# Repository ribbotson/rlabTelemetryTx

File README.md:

rlabTelemetryTx
===============

rlab Telemetry Transmitter

This repository contains code, hardware information and data relating to the rlab Telemetry Transmittter.

The rlab Telemetry Transmitter is an ATXMega128A4U based development board for High altitude Balloon tracking and telemetry.
The transmitter is a Radiometrix NTX2B 434MHz module and the GPS is the Ublox7q. The board is programmed using Atmel DFU over the
USB .

Software is based around the Atmel Software Framework ASF.

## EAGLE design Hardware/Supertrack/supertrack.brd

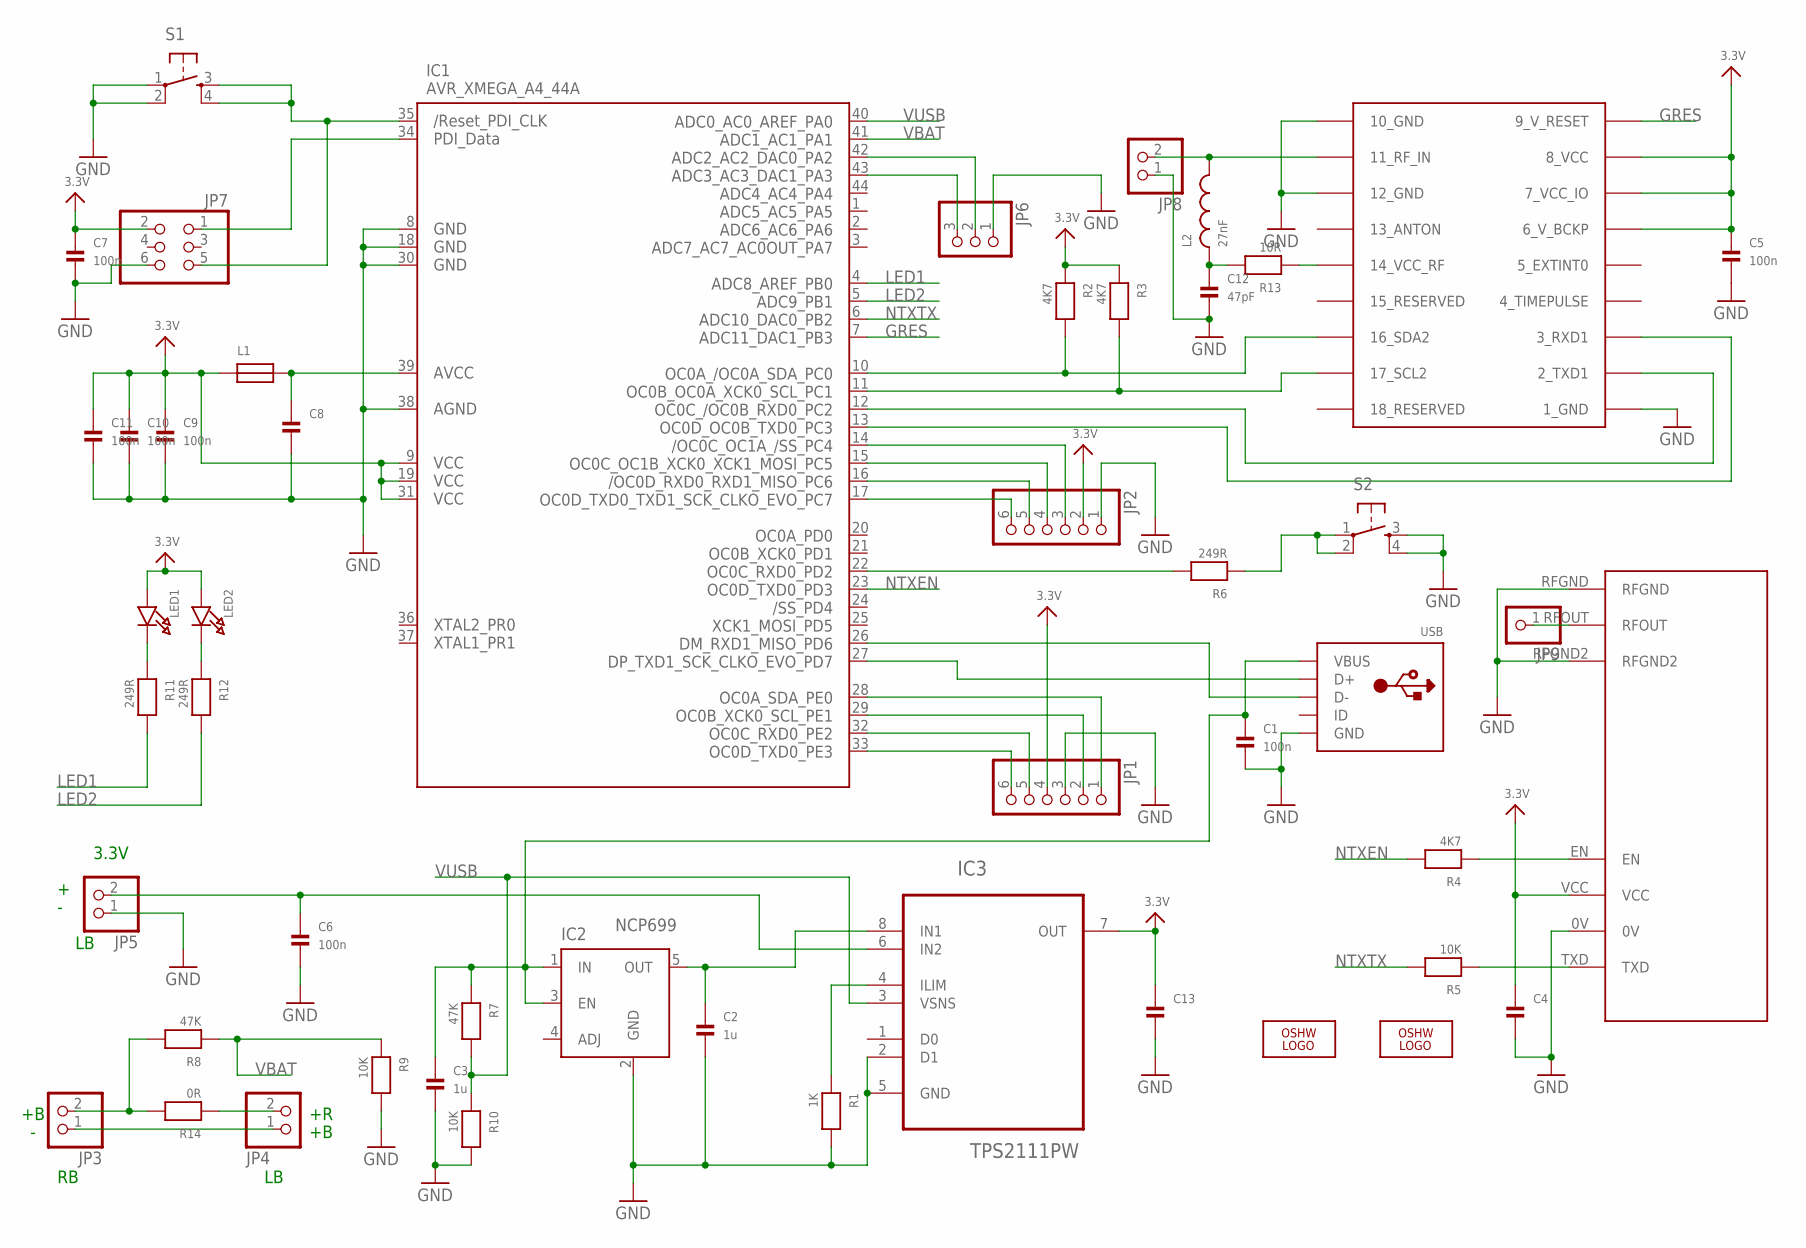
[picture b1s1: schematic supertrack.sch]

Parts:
C1, C5, C6, C7, C9, C10, C11: 100n; 0603
C2, C3: 1u; 0603
C4, C8, C13: CAP_CERAMIC0603; 0603
C12: 47pF; 0603
IC1: AVR_XMEGA_A4_44A; TQFP44
IC2: NCP699; SOT23-5
IC3: TPS2111PW; SOP65P640X120-8N
JP1, JP2: PINHD-1X6; 1X06
JP3, JP4, JP5: PINHD-1X2; 1X02
JP6: PINHD-1X3; 1X03
JP7: PINHD-2X3; 2X03
JP8: HEADER-1X2ROUND; 1X02_ROUND
JP9: HEADER-1X1ROUND; 1X01_ROUND
L1: FERRITE; 0603
L2: 27nF; 0603
LED1, LED2: LED0603; CHIPLED_0603
LOGO1: OSHW_LOGO_8MILX0150-NT; OSHW_8X150_NOTEXT
LOGO2: OSHW_LOGO_8MILX0100-NT; OSHW_8X100_NOTEXT
R1: 1K; 0603
R2, R3, R4: 4K7; 0603
R5, R9, R10: 10K; 0603
R6, R11, R12: 249R; 0603
R7, R8: 47K; 0603
R13: 10R; 0603
R14: 0R; 0603
S1, S2: TAC_SWITCHSMD; TACTILE_SWITCH_SMD
U$1: NTX2
U$2: UBLOX_MAX
USB: USBMINIB; USB-MINIB

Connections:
3.3V: C4.1, C5.1, C7.1, C9.1, C10.1, C11.1, C13.1, IC1.9 (VCC1), IC1.19 (VCC2), IC1.31 (VCC3), IC3.7 (OUT), JP1.4, JP2.2, JP7.2, L1.1, LED1.A, LED2.A, R2.1, R3.1, U$1.VCC, U$2.6_V_BCKP, U$2.7_VCC_IO, U$2.8_VCC
GND: C1.2, C2.2, C3.2, C4.2, C5.2, C6.2, C7.2, C8.2, C9.2, C10.2, C11.2, C12.2, C13.2, IC1.8 (GND1), IC1.18 (GND2), IC1.30 (GND3), IC1.38 (AGND), IC2.2 (GND), IC3.2 (D1), IC3.5 (GND), JP1.3, JP2.1, JP5.1, JP6.1, JP7.6, JP8.1, R1.2, R9.2, R10.2, S1.1, S1.2, S2.3, S2.4, U$1.0V, U$1.RFGND, U$1.RFGND2, U$2.1_GND, U$2.10_GND, U$2.12_GND, USB.GND
GRES: IC1.7 (PB3), U$2.9_V_RESET
LED1: IC1.4 (PB0), R11.2
LED2: IC1.5 (PB1), R12.2
unnamed: C2.1, IC2.5 (OUT), IC3.8 (IN1)
unnamed: IC1.33 (PE3), JP1.6
unnamed: IC1.32 (PE2), JP1.5
unnamed: C6.1, IC3.6 (IN2), JP5.2
unnamed: R6.1, S2.1, S2.2
unnamed: IC1.26 (PD6), USB.D-
unnamed: IC1.27 (PD7), USB.D+
unnamed: IC1.22 (PD2), R6.2
unnamed: R5.1, U$1.TXD
unnamed: R4.1, U$1.EN
unnamed: JP9.1, U$1.RFOUT
unnamed: C1.1, C3.1, IC2.1 (IN), IC2.3 (EN), R7.1, USB.VBUS
unnamed: IC3.4 (ILIM), R1.1
unnamed: IC1.10 (PC0), R2.2, U$2.16_SDA2
unnamed: IC1.11 (PC1), R3.2, U$2.17_SCL2
unnamed: IC1.12 (PC2), U$2.2_TXD1
unnamed: IC1.13 (PC3), U$2.3_RXD1
unnamed: LED2.C, R12.1
unnamed: LED1.C, R11.1
unnamed: IC1.29 (PE1), JP1.2
unnamed: IC1.28 (PE0), JP1.1
unnamed: IC1.17 (PC7), JP2.6
unnamed: IC1.16 (PC6), JP2.5
unnamed: IC1.15 (PC5), JP2.4
unnamed: IC1.14 (PC4), JP2.3
unnamed: JP3.1, JP4.1
unnamed: JP4.2, R14.1
unnamed: IC1.34 (PDI_DATA), JP7.1
unnamed: IC1.35 (RESET), JP7.5, S1.3, S1.4
unnamed: IC1.42 (PA2), JP6.2
unnamed: IC1.43 (PA3), JP6.3
unnamed: JP8.2, L2.2, U$2.11_RF_IN
unnamed: C12.1, L2.1, R13.2
unnamed: R13.1, U$2.14_VCC_RF
unnamed: C8.1, IC1.39 (AVCC), L1.2
NTXEN: IC1.23 (PD3), R4.2
NTXTX: IC1.6 (PB2), R5.2
VBAT: IC1.41 (PA1), R8.1, R9.1
VIN: JP3.2, R8.2, R14.2
VUSB: IC1.40 (PA0), IC3.3 (VSNS), R7.2, R10.1

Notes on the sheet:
3.3V

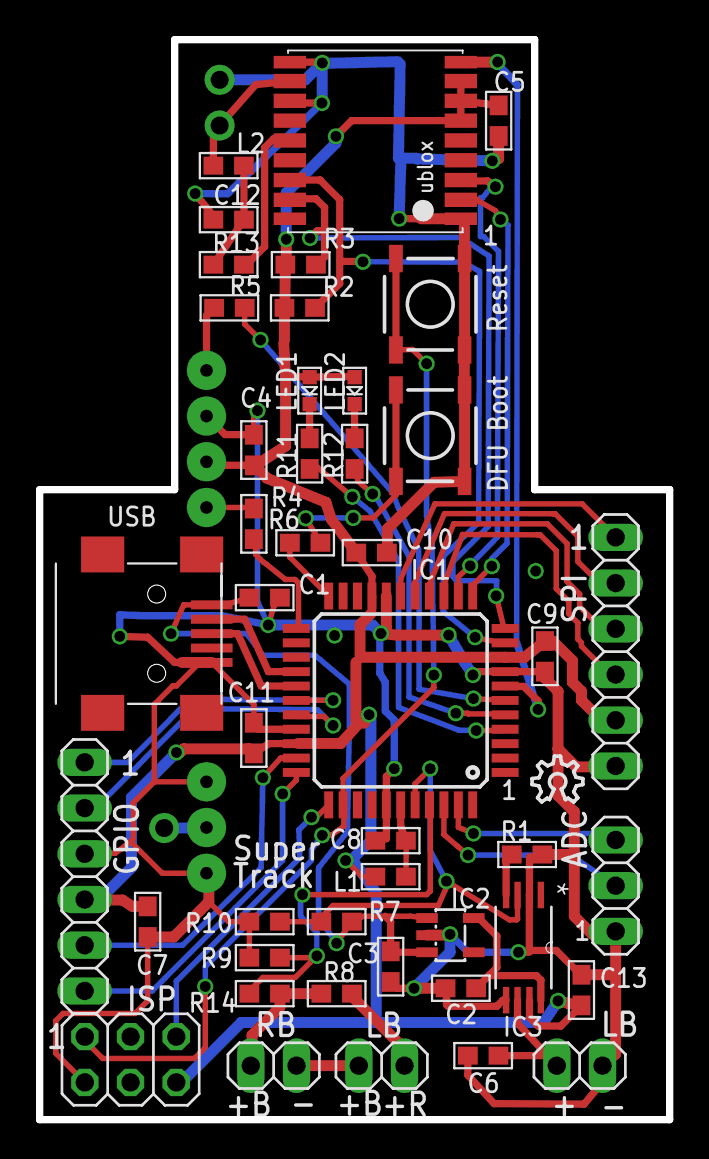
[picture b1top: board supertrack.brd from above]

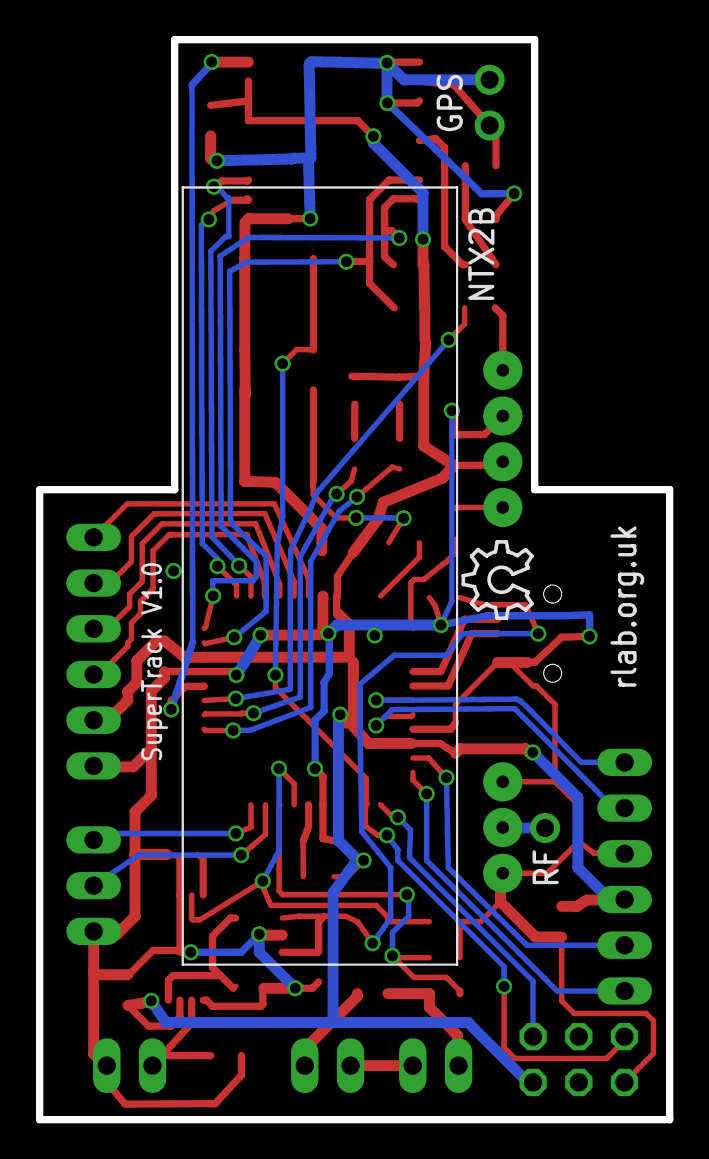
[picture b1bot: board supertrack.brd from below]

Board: 2 copper layers, 35.0 x 60.0 mm, 50 parts (2 on the bottom side), 45 nets.

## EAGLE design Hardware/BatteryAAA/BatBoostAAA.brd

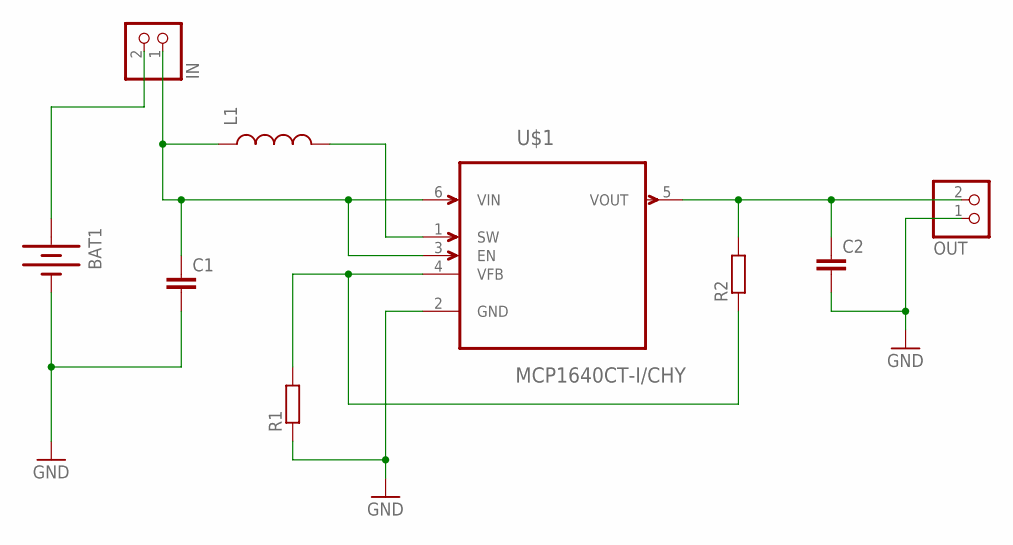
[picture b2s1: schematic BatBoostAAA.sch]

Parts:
BAT1: BATTERYAAA; BATTERY-AAA
C1, C2: C-EUC0805K; C0805K
IN: PINHD-1X2; 1X02
L1: INDUCTOR1210; LQH32
OUT: PINHD-1X2; 1X02
R1, R2: R-EU_R0603; R0603
U$1: MCP1640CT-I/CHY; SOT95P270X145-6N

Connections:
GND: BAT1.GND@1 (-), C1.2, C2.2, OUT.1, R1.1, U$1.2 (GND)
unnamed: C1.1, IN.1, L1.1, U$1.3 (EN), U$1.6 (VIN)
unnamed: C2.1, OUT.2, R2.2, U$1.5 (VOUT)
unnamed: R1.2, R2.1, U$1.4 (VFB)
unnamed: L1.2, U$1.1 (SW)
unnamed: BAT1.PWR@1 (+), IN.2

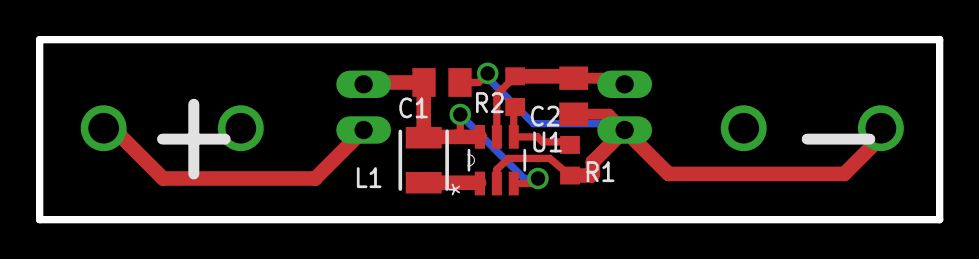
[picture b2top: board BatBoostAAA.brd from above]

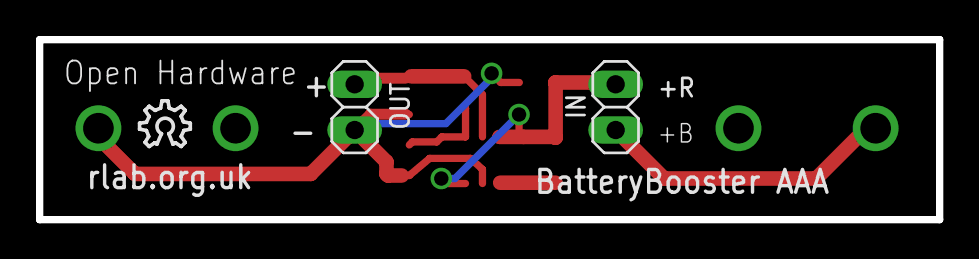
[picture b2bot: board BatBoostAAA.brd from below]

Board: 2 copper layers, 50.0 x 10.0 mm, 10 parts (3 on the bottom side), 6 nets.

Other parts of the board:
U$2: OSHW_8X100_NOTEXT

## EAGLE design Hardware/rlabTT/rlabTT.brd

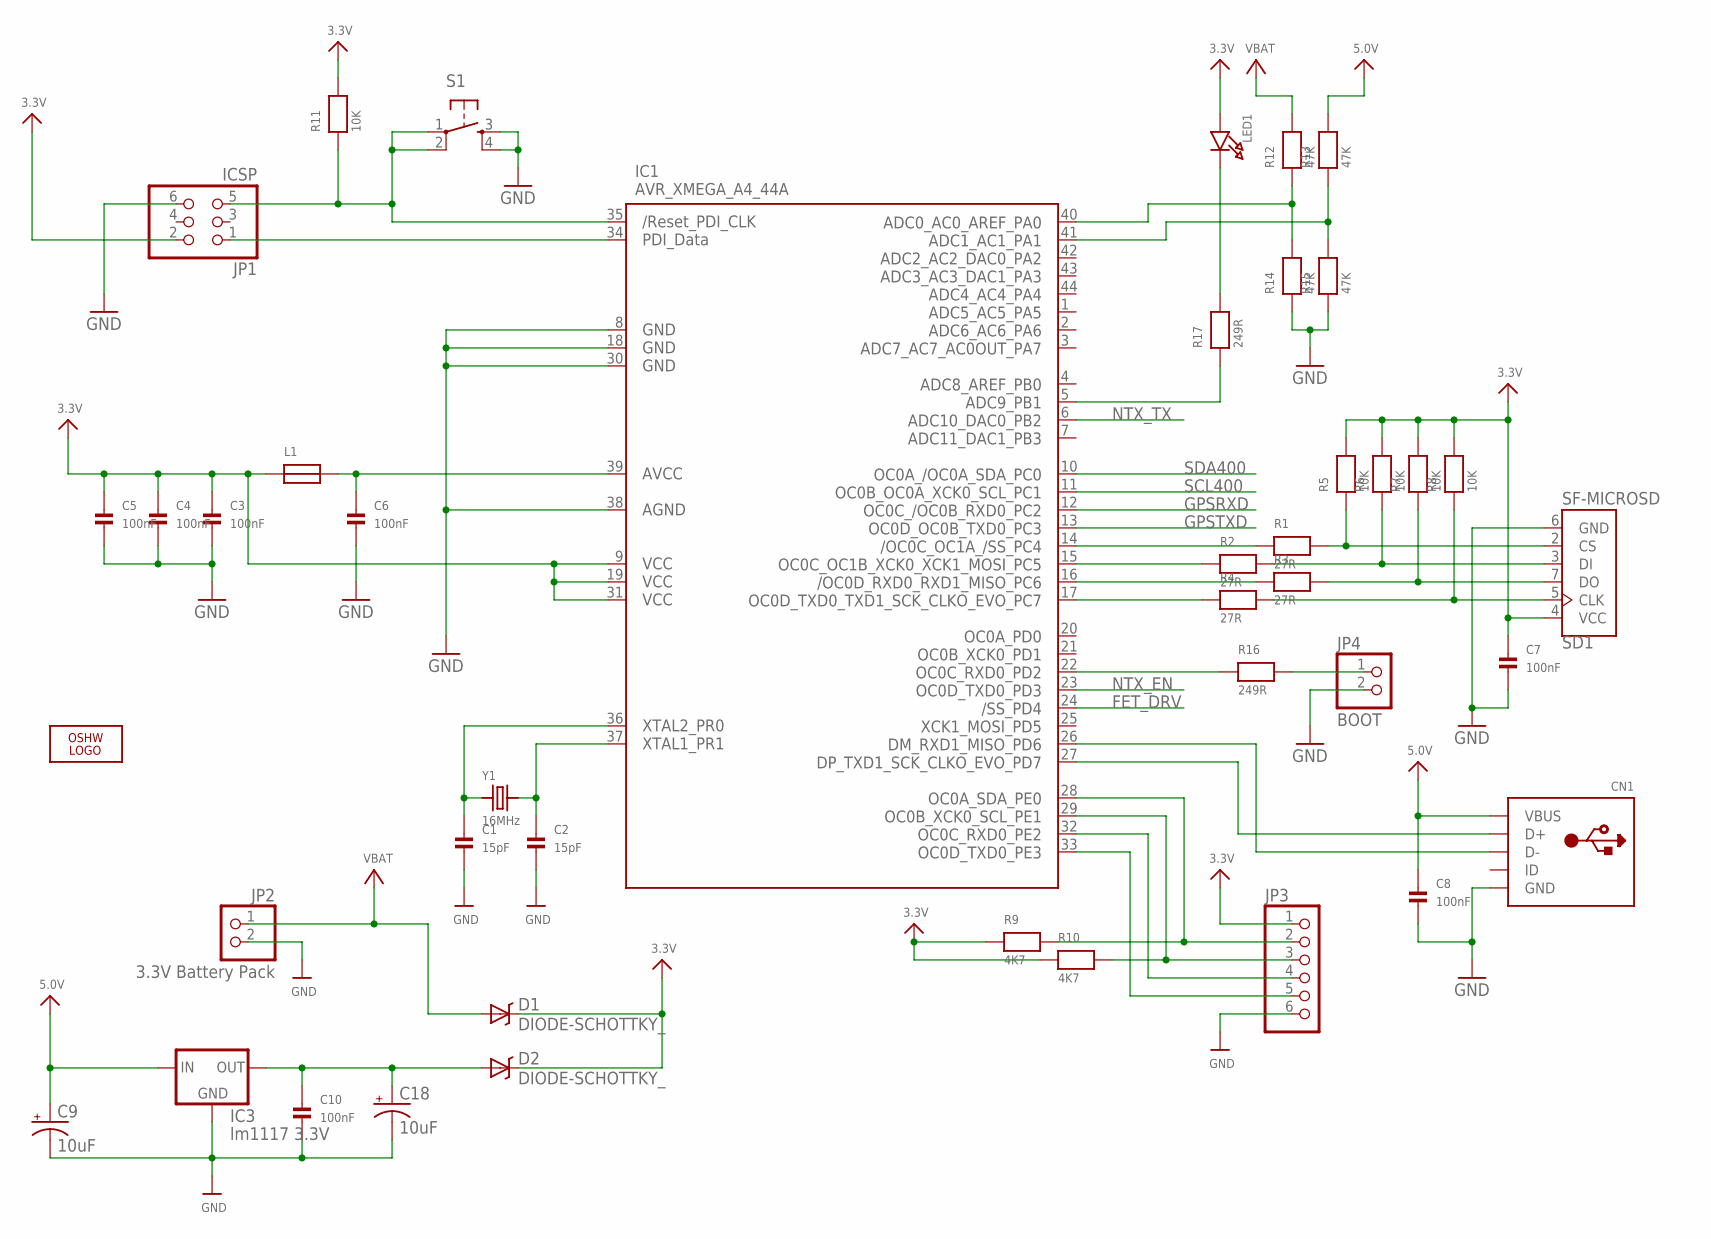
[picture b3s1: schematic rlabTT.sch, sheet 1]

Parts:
C1, C2: 15pF; 0603
C3, C4, C5, C6, C7, C8, C10: 100nF; 0603
C9, C18: 10uF; EIA3528
CN1: USBMINIB; USB-MINIB
D1, D2: DIODE-SCHOTTKY_; SMA-DIODE
IC1: AVR_XMEGA_A4_44A; TQFP44
IC3: lm1117 3.3V; SOT223
JP1: ICSP; 2X03/90
JP2: 3.3V Battery Pack; 1X02/90
JP3: PINHD-1X6/90; 1X06/90
JP4: BOOT; 1X02/90
L1: FERRITE; 0603
LED1: LED0603; CHIPLED_0603
LOGO1: OSHW_LOGO_8MILX0150-NT; OSHW_8X150_NOTEXT
R1, R2, R3, R4: 27R; 0603
R5, R6, R7, R8, R11: 10K; 0603
R9, R10: 4K7; 0603
R12, R13, R14, R15: 47K; 0603
R16, R17: 249R; 0603
S1: TAC_SWITCHSMD; TACTILE_SWITCH_SMD
SD1: SF-MICROSD; MICROSD
Y1: 16MHz; CRYSTAL_3.2X2.5

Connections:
3.3V: C3.1, C4.1, C5.1, C7.1, D1.C, D2.C, IC1.9 (VCC1), IC1.19 (VCC2), IC1.31 (VCC3), JP1.2, JP3.1, L1.1, LED1.A, R5.2, R6.2, R7.2, R8.2, R9.1, R10.1, R11.2, SD1.4 (VCC); also elsewhere on the board
5.0V: C8.1, C9.A (+), CN1.VBUS, IC3.3 (IN), R13.2
FET_DRV: IC1.24 (PD4); also elsewhere on the board
GND: C1.2, C2.2, C3.2, C4.2, C5.2, C6.2, C7.2, C8.2, C9.C (-), C10.2, C18.C (-), CN1.GND, IC1.8 (GND1), IC1.18 (GND2), IC1.30 (GND3), IC1.38 (AGND), IC3.1 (GND), JP1.6, JP2.2, JP3.6, JP4.2, R14.1, R15.1, S1.3, S1.4, SD1.6 (GND); also elsewhere on the board
GPSRXD: IC1.12 (PC2); also elsewhere on the board
GPSTXD: IC1.13 (PC3); also elsewhere on the board
unnamed: IC1.40 (PA0), R12.1, R14.2
unnamed: IC1.22 (PD2), R16.1
unnamed: IC1.41 (PA1), R13.1, R15.2
unnamed: JP4.1, R16.2
unnamed: IC1.5 (PB1), R17.1
unnamed: LED1.C, R17.2
unnamed: C2.1, IC1.37 (PR1), Y1.2
unnamed: C1.1, IC1.36 (PR0), Y1.1
unnamed: C6.1, IC1.39 (AVCC), L1.2
unnamed: IC1.14 (PC4), R1.1
unnamed: CN1.D+, IC1.27 (PD7)
unnamed: CN1.D-, IC1.26 (PD6)
unnamed: IC1.15 (PC5), R2.1
unnamed: IC1.16 (PC6), R3.1
unnamed: IC1.17 (PC7), R4.1
unnamed: R1.2, R5.1, SD1.2 (CS)
unnamed: R2.2, R6.1, SD1.3 (DI)
unnamed: R3.2, R7.1, SD1.7 (DO)
unnamed: IC1.35 (RESET), JP1.5, R11.1, S1.1, S1.2
unnamed: IC1.34 (PDI_DATA), JP1.1
unnamed: C10.1, C18.A (+), D2.A, IC3.2 (OUT)
unnamed: IC1.28 (PE0), JP3.2, R9.2
unnamed: IC1.29 (PE1), JP3.3, R10.2
unnamed: IC1.32 (PE2), JP3.4
unnamed: IC1.33 (PE3), JP3.5
NTX_EN: IC1.23 (PD3); also elsewhere on the board
NTX_TX: IC1.6 (PB2); also elsewhere on the board
SCL400: IC1.11 (PC1); also elsewhere on the board
SD1: R4.2, R8.1, SD1.5 (CLK)
SDA400: IC1.10 (PC0); also elsewhere on the board
VBAT: D1.A, JP2.1, R12.2

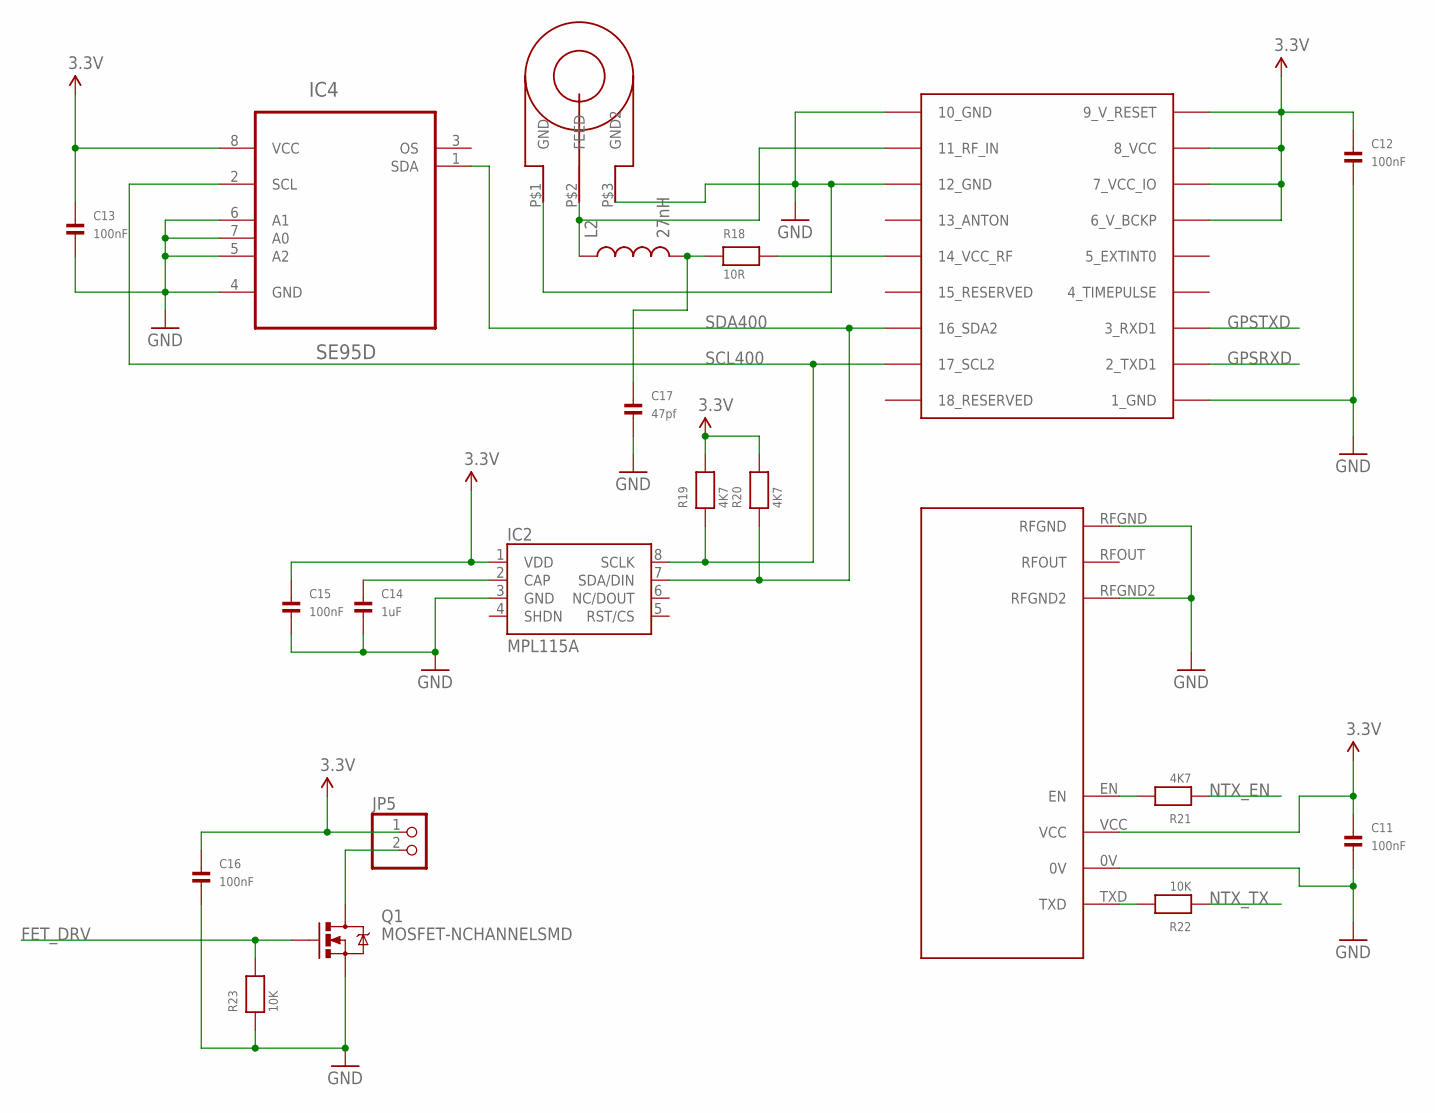
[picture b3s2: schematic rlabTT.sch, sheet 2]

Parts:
C11, C12, C13, C15, C16: 100nF; 0603
C14: 1uF; 0603
C17: 47pf; 0603
IC2: MPL115A; LGA8
IC4: SE95D; SOIC127P600X175-8N
JP5: PINHD-1X2/90; 1X02/90
L2: 27nH; 0603
Q1: MOSFET-NCHANNELSMD; SOT23-3
R18: 10R; 0603
R19, R20, R21: 4K7; 0603
R22, R23: 10K; 0603
U1: UBLOX_MAX
U2: NTX2
U3: SARANTEL-SL1250

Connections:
3.3V: C11.1, C12.1, C13.1, C15.1, C16.1, IC2.1 (VDD), IC4.8 (VCC), JP5.1, R19.2, R20.2, U1.6_V_BCKP, U1.7_VCC_IO, U1.8_VCC, U1.9_V_RESET, U2.VCC; also elsewhere on the board
FET_DRV: Q1.1 (G), R23.2; also elsewhere on the board
GND: C11.2, C12.2, C13.2, C14.2, C15.2, C16.2, C17.2, IC2.3 (GND), IC4.4 (GND), IC4.5 (A2), IC4.6 (A1), IC4.7 (A0), Q1.2 (S), R23.1, U1.1_GND, U1.10_GND, U1.12_GND, U2.0V, U2.RFGND, U2.RFGND2, U3.P$1 (GND), U3.P$3 (GND2); also elsewhere on the board
GPSRXD: U1.2_TXD1; also elsewhere on the board
GPSTXD: U1.3_RXD1; also elsewhere on the board
unnamed: L2.1, U1.11_RF_IN, U3.P$2 (FEED)
unnamed: R21.2, U2.EN
unnamed: R18.2, U1.14_VCC_RF
unnamed: C17.1, L2.2, R18.1
unnamed: R22.2, U2.TXD
unnamed: JP5.2, Q1.3 (D)
unnamed: C14.1, IC2.2 (CAP)
NTX_EN: R21.1; also elsewhere on the board
NTX_TX: R22.1; also elsewhere on the board
SCL400: IC2.8 (SCLK), IC4.2 (SCL), R19.1, U1.17_SCL2; also elsewhere on the board
SDA400: IC2.7 (SDA/DIN), IC4.1 (SDA), R20.1, U1.16_SDA2; also elsewhere on the board

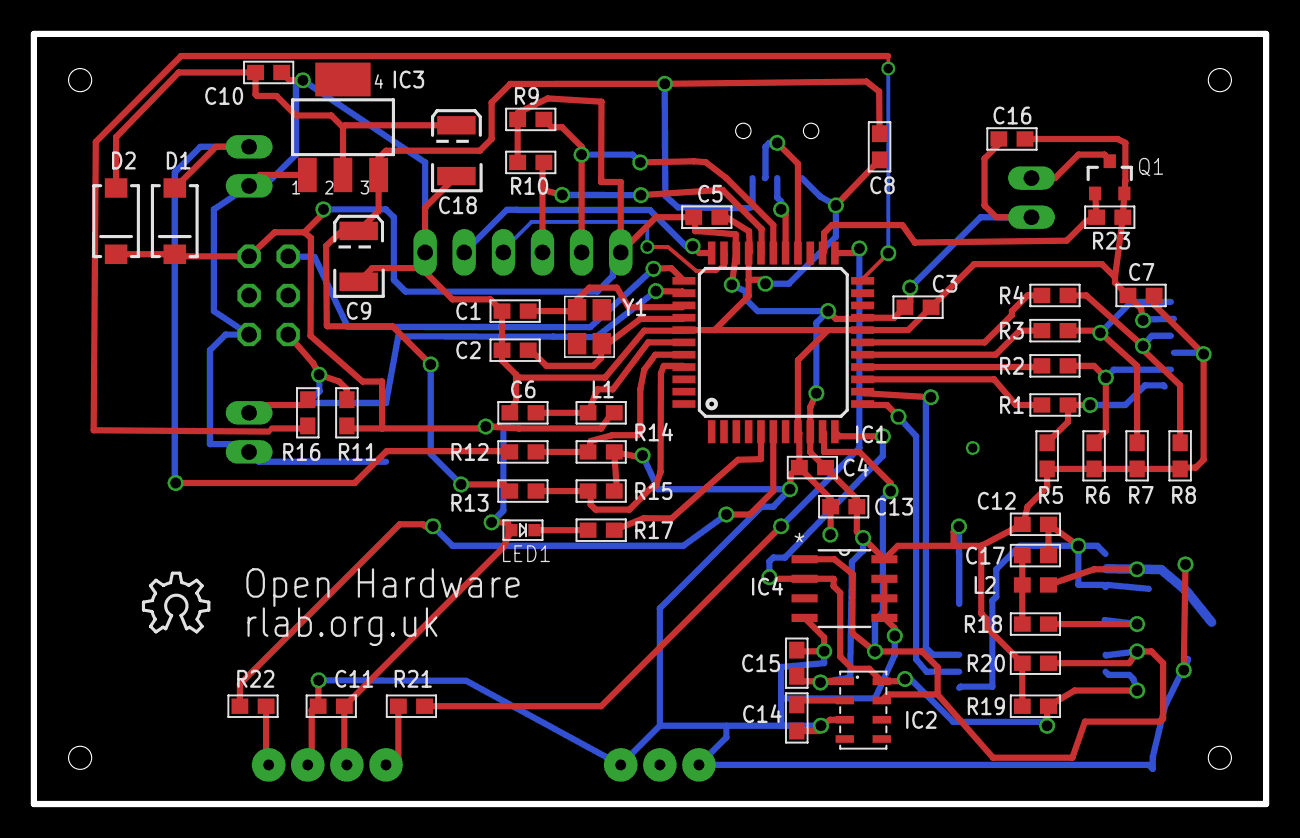
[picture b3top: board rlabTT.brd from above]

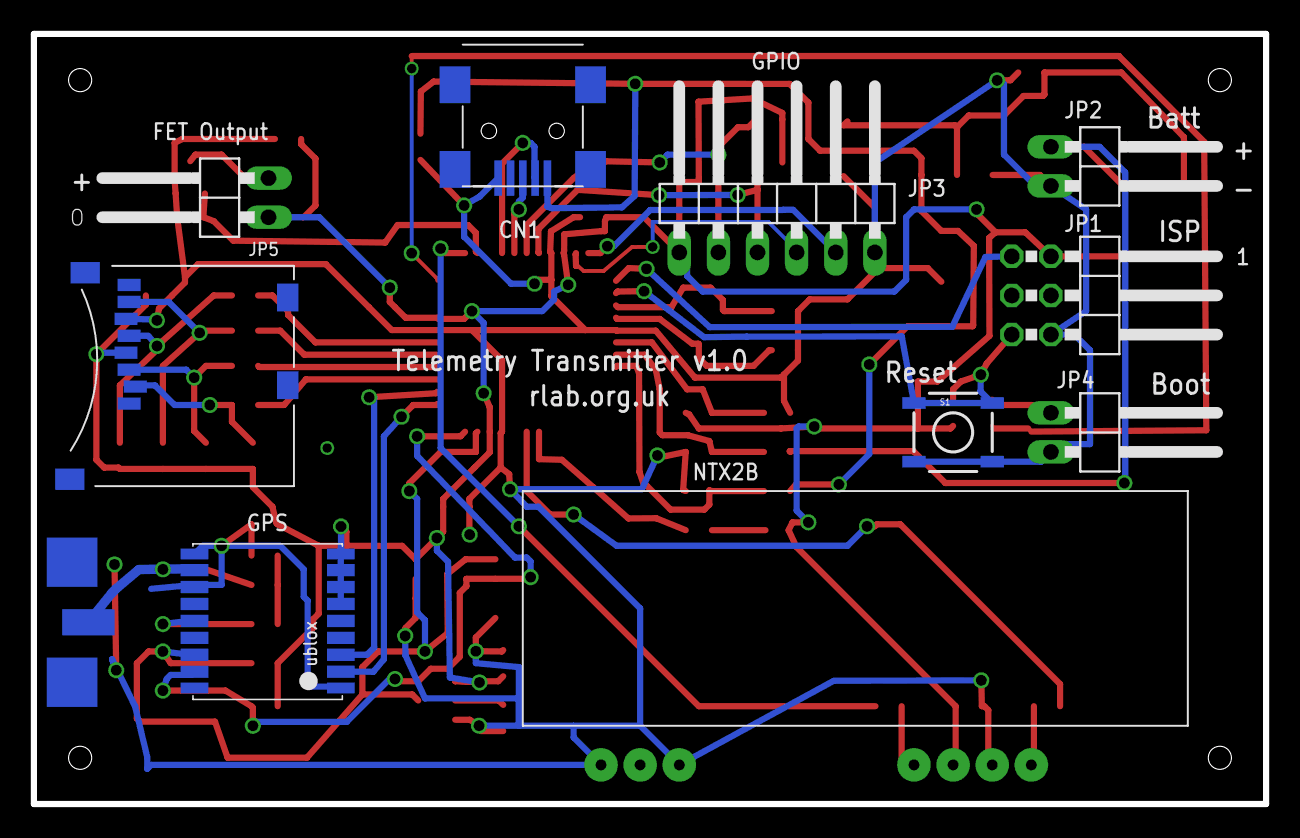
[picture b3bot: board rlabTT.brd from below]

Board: 2 copper layers, 80.0 x 50.0 mm, 64 parts (11 on the bottom side), 44 nets.

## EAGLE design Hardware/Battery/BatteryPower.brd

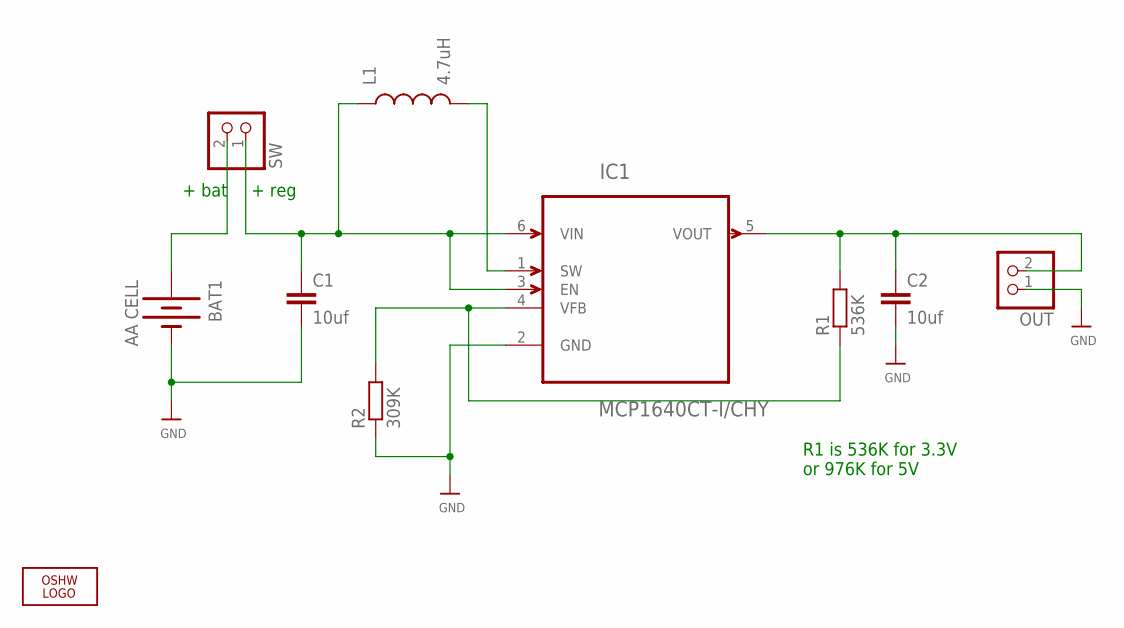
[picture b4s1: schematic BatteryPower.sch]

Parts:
BAT1: AA CELL; BATTERY-AA
C1, C2: 10uf; C0805
IC1: MCP1640CT-I/CHY; SOT95P270X145-6N
L1: 4.7uH; CR75
LOGO1: OSHW_LOGO_8MILX0150-NT; OSHW_8X150_NOTEXT
OUT: PINHD-1X2/90; 1X02/90
R1: 536K; R0603
R2: 309K; R0603
SW: PINHD-1X2/90; 1X02/90

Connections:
GND: BAT1.GND@1 (-), C1.2, C2.2, IC1.2 (GND), OUT.1, R2.1
unnamed: C1.1, IC1.3 (EN), IC1.6 (VIN), L1.P$1 (1), SW.1
unnamed: IC1.1 (SW), L1.P$2 (2)
unnamed: IC1.4 (VFB), R1.1, R2.2
unnamed: C2.1, IC1.5 (VOUT), OUT.2, R1.2
unnamed: BAT1.PWR@1 (+), SW.2

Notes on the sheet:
+ bat
+ reg
R1 is 536K for 3.3V or 976K for 5V

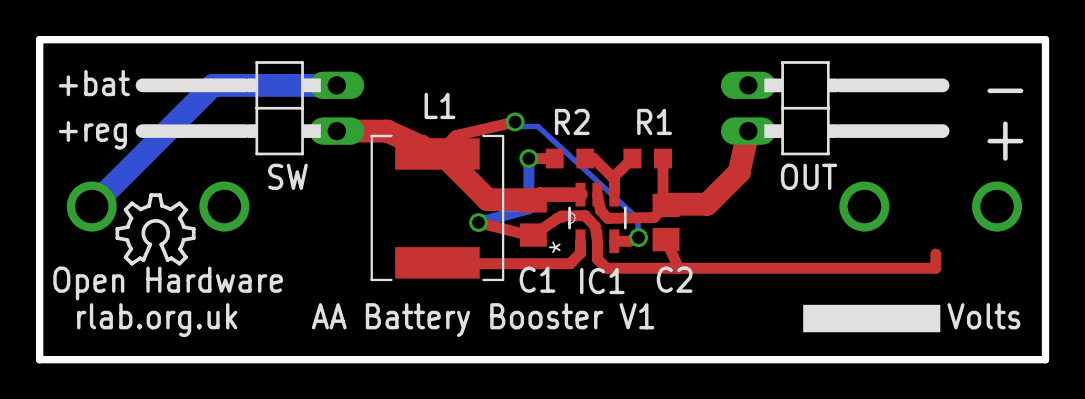
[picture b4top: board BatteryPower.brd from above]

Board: 2 copper layers, 55.9 x 17.8 mm, 10 parts (1 on the bottom side), 6 nets.

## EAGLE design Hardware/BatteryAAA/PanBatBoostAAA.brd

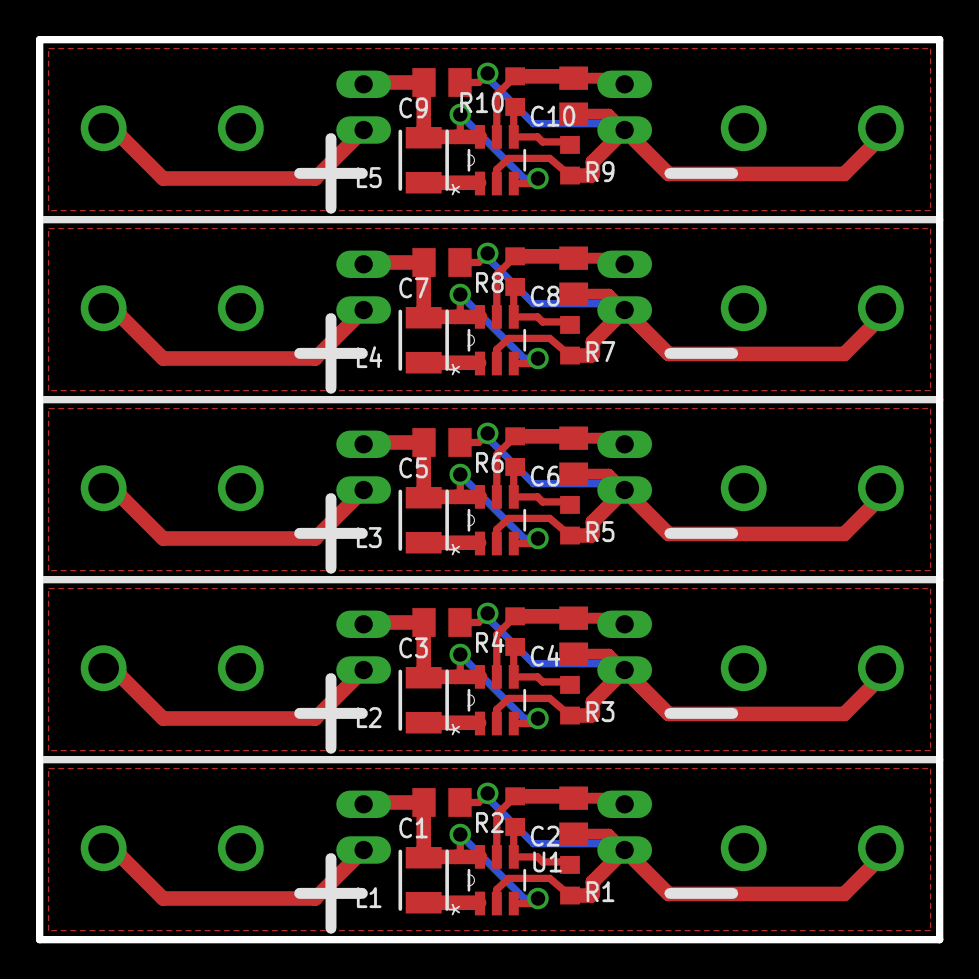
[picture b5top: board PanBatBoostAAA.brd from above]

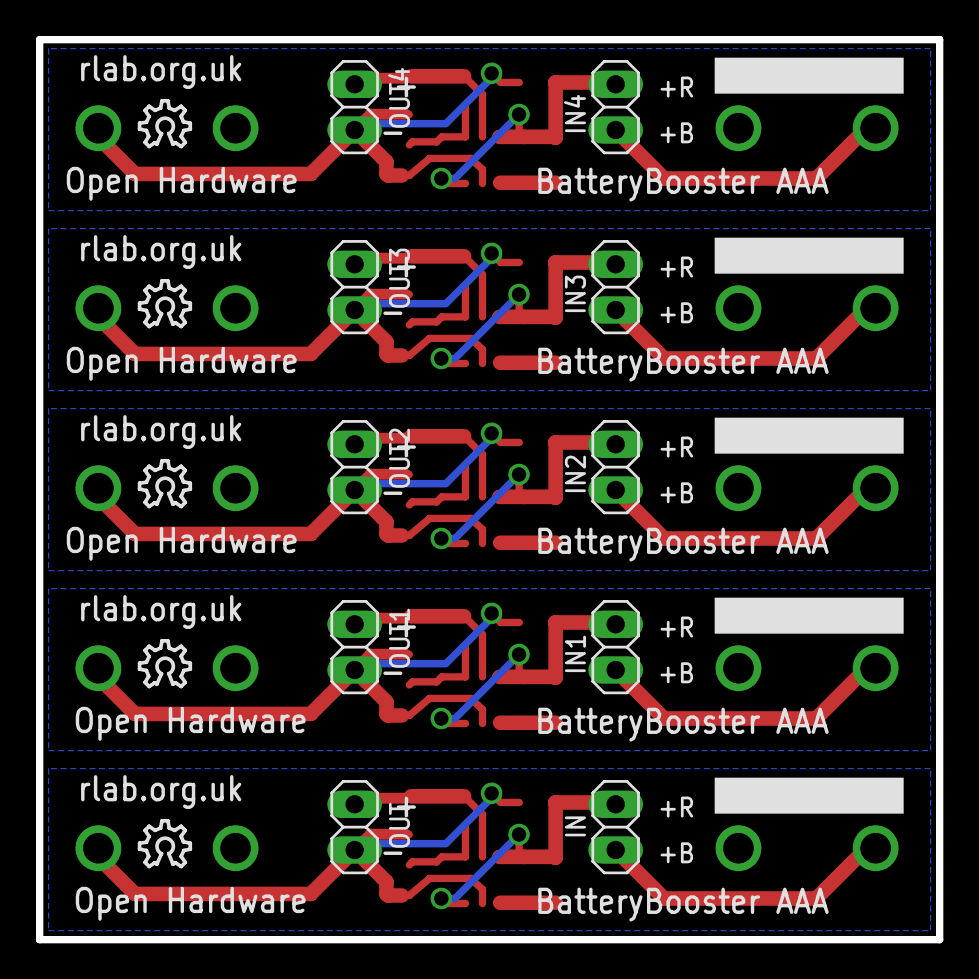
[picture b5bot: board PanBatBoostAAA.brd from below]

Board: 2 copper layers, 50.0 x 50.0 mm, 50 parts (15 on the bottom side), 30 nets.

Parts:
BAT1, BAT2, BAT3, BAT4, BAT5: BATTERY-AAA
C1, C2, C3, C4, C5, C6, C7, C8, C9, C10: C0805K
IN, IN1, IN2, IN3, IN4: 1X02
L1, L2, L3, L4, L5: LQH32
OUT, OUT1, OUT2, OUT3, OUT4: 1X02
R1, R2, R3, R4, R5, R6, R7, R8, R9, R10: R0603
U$1, U$3, U$5, U$7, U$9: MCP1640CT-I/CHY; SOT95P270X145-6N
U$2, U$4, U$6, U$8, U$10: OSHW_8X100_NOTEXT

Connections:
GND: BAT1.GND@1, C1.2, C2.2, OUT.1, R1.1, U$1.2
GND1: BAT2.GND@1, C3.2, C4.2, OUT1.1, R3.1, U$3.2
GND2: BAT3.GND@1, C5.2, C6.2, OUT2.1, R5.1, U$5.2
GND3: BAT4.GND@1, C7.2, C8.2, OUT3.1, R7.1, U$7.2
GND4: BAT5.GND@1, C9.2, C10.2, OUT4.1, R9.1, U$9.2
unnamed: C1.1, IN.1, L1.1, U$1.3, U$1.6
unnamed: C2.1, OUT.2, R2.2, U$1.5
unnamed: R1.2, R2.1, U$1.4
unnamed: L1.2, U$1.1
unnamed: BAT1.PWR@1, IN.2
unnamed: C4.1, OUT1.2, R4.2, U$3.5
unnamed: R3.2, R4.1, U$3.4
unnamed: BAT2.PWR@1, IN1.2
unnamed: C3.1, IN1.1, L2.1, U$3.3, U$3.6
unnamed: L2.2, U$3.1
unnamed: C6.1, OUT2.2, R6.2, U$5.5
unnamed: R5.2, R6.1, U$5.4
unnamed: BAT3.PWR@1, IN2.2
unnamed: C5.1, IN2.1, L3.1, U$5.3, U$5.6
unnamed: L3.2, U$5.1
unnamed: C8.1, OUT3.2, R8.2, U$7.5
unnamed: R7.2, R8.1, U$7.4
unnamed: BAT4.PWR@1, IN3.2
unnamed: C7.1, IN3.1, L4.1, U$7.3, U$7.6
unnamed: L4.2, U$7.1
unnamed: C10.1, OUT4.2, R10.2, U$9.5
unnamed: R9.2, R10.1, U$9.4
unnamed: BAT5.PWR@1, IN4.2
unnamed: C9.1, IN4.1, L5.1, U$9.3, U$9.6
unnamed: L5.2, U$9.1

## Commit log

2014-07-01 rlab Telemetry Transceiver Development Board
    ATXMega128A4U Development board for High Altitude Balloon Telemetry
    Transmitter using NTX2B 434MHz transmitter and Ublox7Q GPS
2014-07-01 First Post of Battery Board
    Battery Holder with boost regulator
2014-07-01 First Post for XMega Development Board
    ATXMega128A4U Telemetry Transmitter Board with NTX2B 434MHz transmitter
    and ublox7Q GPS
2014-07-01 DFU Bootloader for rlab Telemetry Transmitter board
    Modified bootloader for rlab Telemetry Transmitter to use pin PD2 as the
    boot enable input.
2014-07-01 Modified conf.isp.h file to use the input PD2 for boot
    Conf.isp.h file is modified to use a different pin on the rlab Telemetry
    Transmitter board.
    Source for bootloader is available from Atmel and built using the IAR
    workbench.
    Hex file is downloader to ATXMega using PDI programmer. ATXMega128A4U
    devices are supplied by Atmel with no bootloader present.
2014-07-01 First submission of utility for Ublox Ucentre
    This utility connects the rlabTT GPS to the USB CDC port to enable Ublox
    Ucentre to communicate direct to GPS.
2014-07-01 Add PDFs of schematics
2014-07-01 Add PDF of schematic
2014-07-14 Add First submission of rlabTT CDC
    Submission of development software for rlab Telemetry Transmitter board
2014-08-06 Add first submission of rlabtt-Beacon
    rlabtt-Beacon is RTTY beacon with GPS and other telemetry data
2014-08-19 PCB for Superman tracker and batteries
    Smaller boards to go inside body cavity of model
2014-08-27 Update to latest ASF, Add EEPROM routines
    Update ASF to 3.19.0
    Add EEPROM to get configuration on startup
2014-08-27 Add Port selection at start up
    Add code to determine if USB or external serial is used at start up,
    based on configuration and power source

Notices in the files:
parts and their libraries:
SparkFun: Licensing: CC v3.0 Share-Alike You are welcome to use this library for commercial purposes.
microbuilder: This work is placed in the public domain, and may be freely used for commercial and non-commercial work with the following conditions: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
